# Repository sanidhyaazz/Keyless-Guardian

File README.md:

<h1>Keyless Guardian</h1>

<p>The project aims at implementing a system to mark attendance and grant access to the A.T.O.M. Robotics Laboratory to its members using rfid mechanism that checks the database managed at mongoDB for validating rfid card provided to the members.
It uses hardware technologies like esp32, rfid sensors and pcb designed and managed by the members of the club.
</p>

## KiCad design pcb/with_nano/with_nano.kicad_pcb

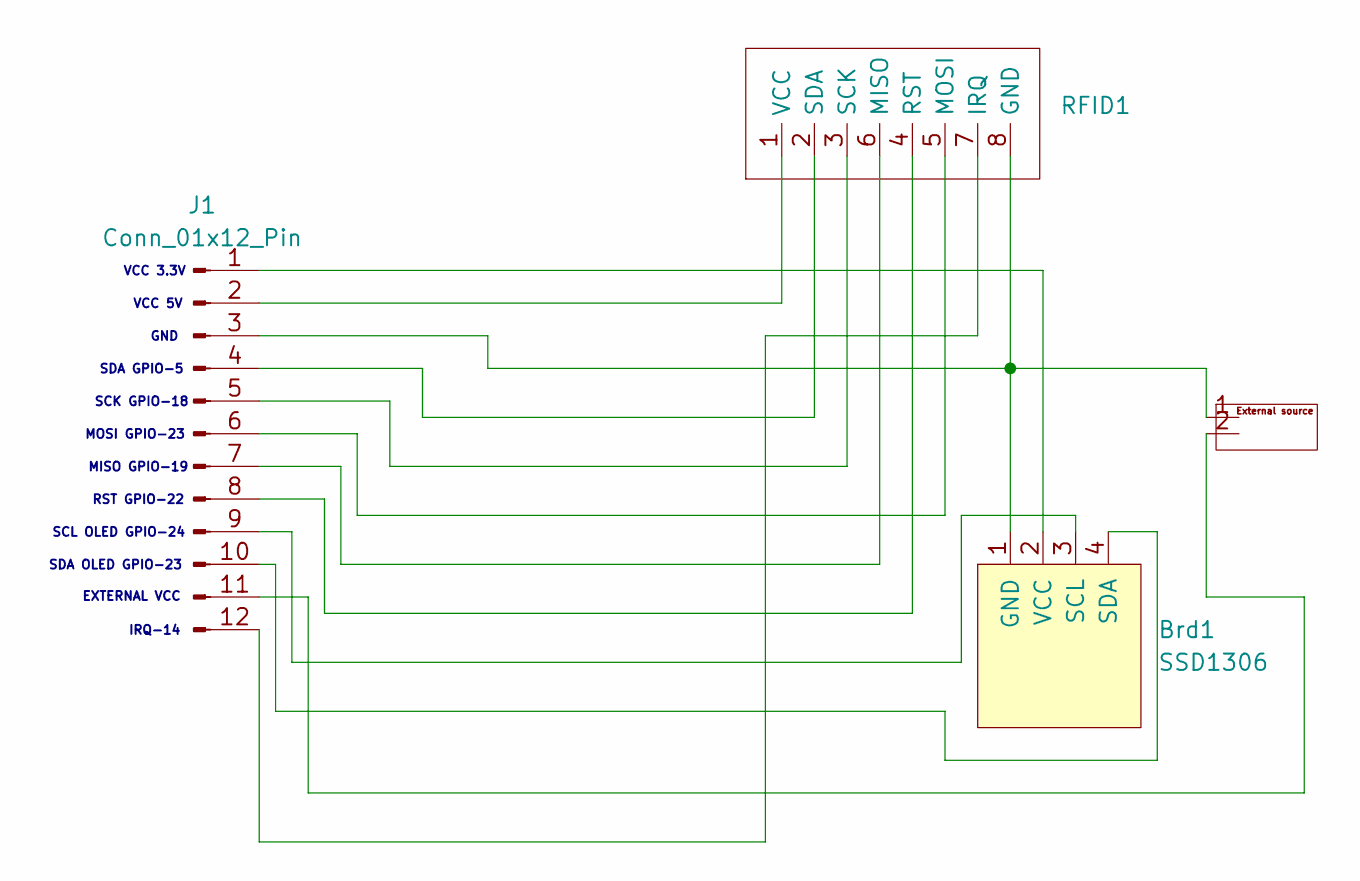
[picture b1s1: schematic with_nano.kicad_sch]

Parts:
Brd1: SSD1306; Adafruit_SSD1306
J1: Conn_01x12_Pin; PinHeader_1x12_P1.00mm_Vertical
RFID1: RFID-RC522
U1: PinSocket_1x02_P1.00mm_Vertical

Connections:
unnamed: Brd1.1 (GND), J1.3, RFID1.8 (GND), U1.1
unnamed: Brd1.3 (SCL), J1.9
unnamed: Brd1.4 (SDA), J1.10
unnamed: Brd1.2 (VCC), J1.1
unnamed: J1.2, RFID1.1 (VCC)
unnamed: J1.4, RFID1.2 (SDA)
unnamed: J1.5, RFID1.3 (SCK)
unnamed: J1.6, RFID1.5 (MOSI)
unnamed: J1.7, RFID1.6 (MISO)
unnamed: J1.8, RFID1.4 (RST)
unnamed: J1.11, U1.2
unnamed: J1.12, RFID1.7 (IRQ)

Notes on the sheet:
MISO GPIO-19
IRQ-14
RST GPIO-22
SDA GPIO-5
SCK GPIO-18
EXTERNAL VCC
GND
SDA OLED GPIO-23
VCC 5V
MOSI GPIO-23
SCL OLED GPIO-24
VCC 3.3V

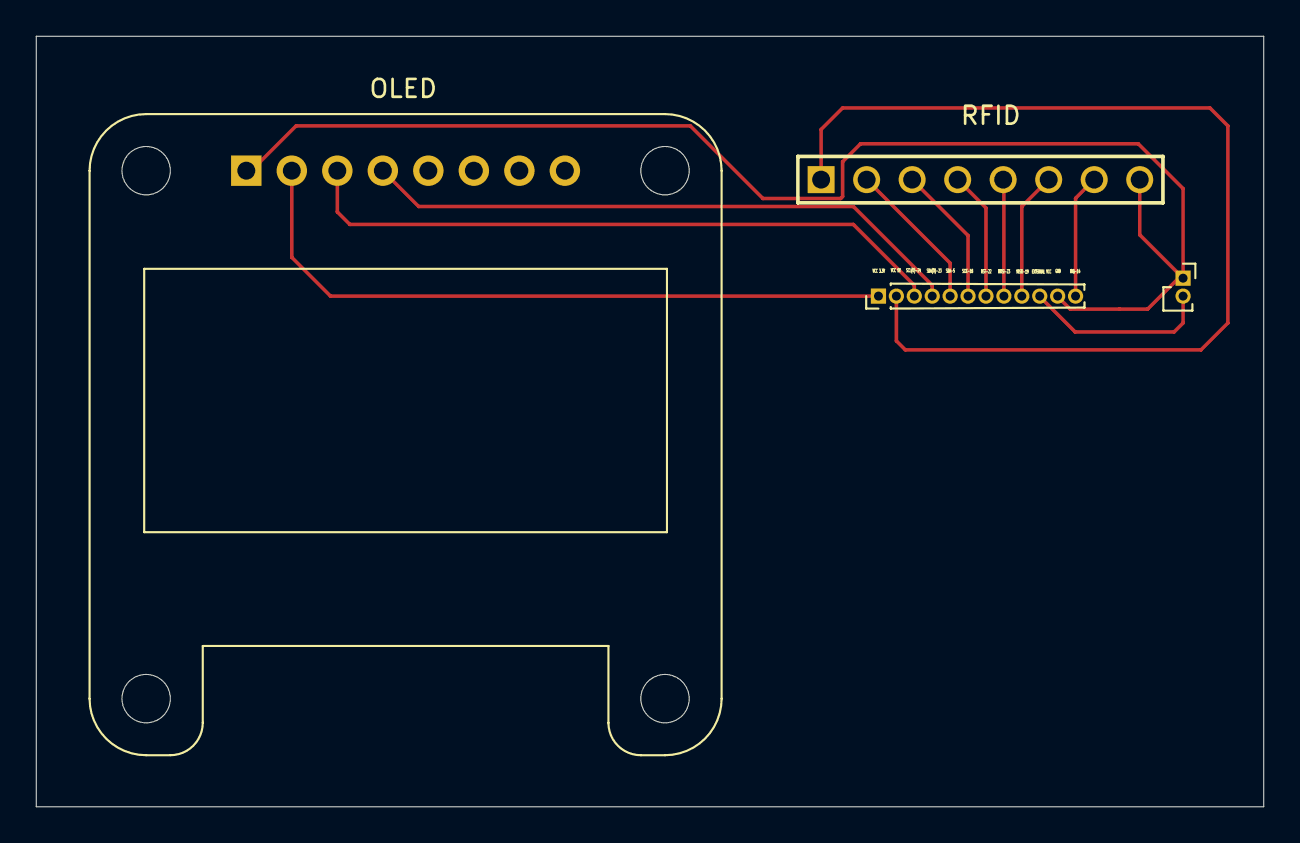
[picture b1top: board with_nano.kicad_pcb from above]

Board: 2 copper layers, 68.5 x 43.0 mm, 4 parts (0 on the bottom side), 12 nets.

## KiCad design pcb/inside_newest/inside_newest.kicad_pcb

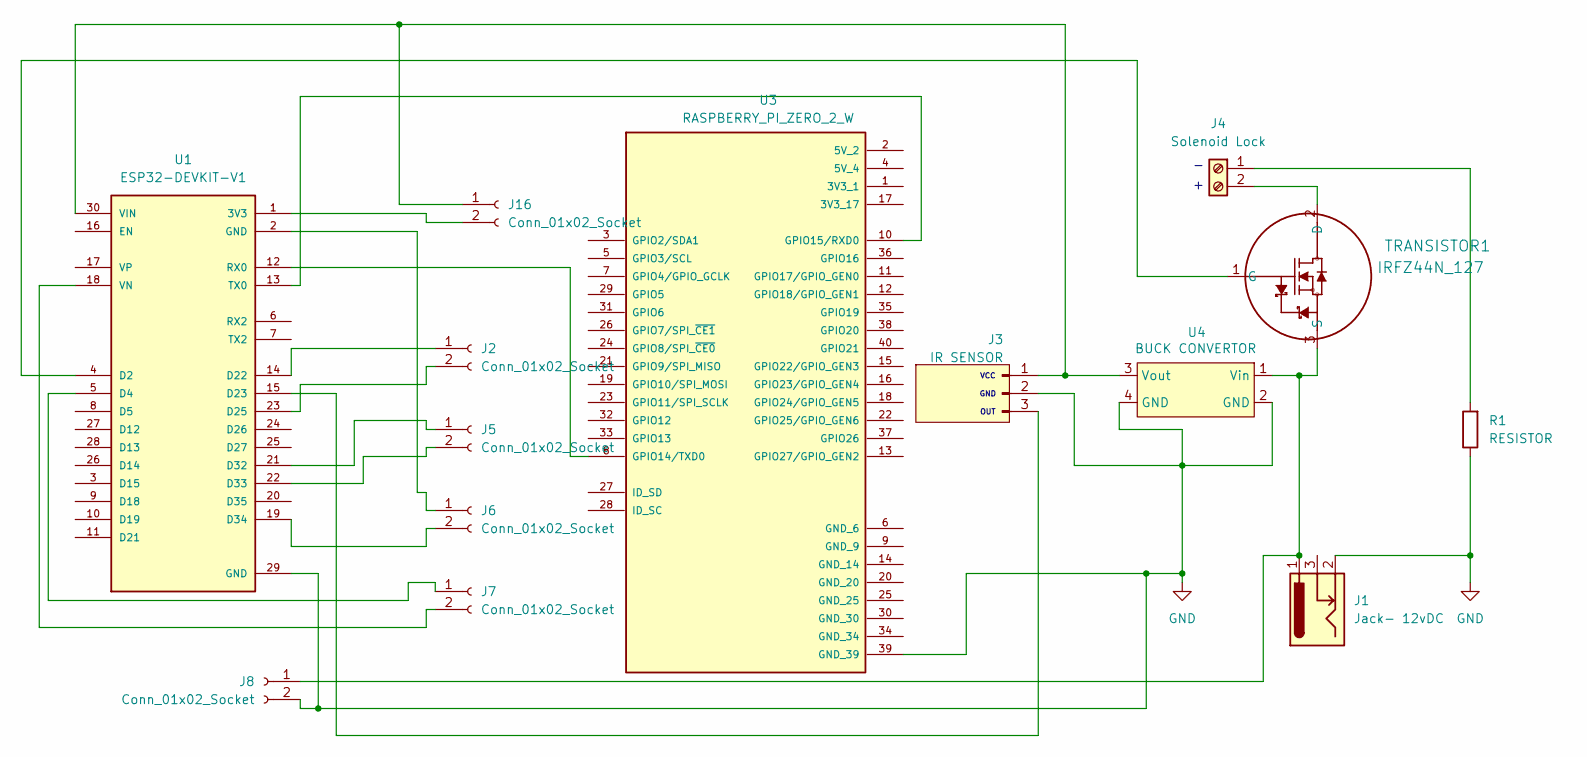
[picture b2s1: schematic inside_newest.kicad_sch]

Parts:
J1: Jack- 12vDC; NINIGI_DC-005
J2, J5, J6, J7, J8, J16: Conn_01x02_Socket; PinSocket_1x02_P1.00mm_Vertical
J3: IR SENSOR; PinSocket_1x03_P1.00mm_Vertical
J4: Solenoid Lock; TerminalBlock_bornier-2_P5.08mm
R1: RESISTOR; PinSocket_1x02_P1.00mm_Vertical
TRANSISTOR1: IRFZ44N_127; SOT78_TO220_NXP
U1: ESP32-DEVKIT-V1; MODULE_ESP32_DEVKIT_V1; PARTREV N/A
U3: RASPBERRY_PI_ZERO_2_W; MODULE_RASPBERRY_PI_ZERO_2_W; PARTREV April 2024
U4: BUCK CONVERTOR; LM2596 DC TO DC BUCK CONVERTER FOOTPRINT

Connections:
GND: J1.2, J3.2, J8.2, R1.1, U1.29 (GND), U3.39 (GND_39), U4.2 (GND), U4.4 (GND)
unnamed: J2.1, U1.14 (D22)
unnamed: J2.2, U1.23 (D25)
unnamed: J3.3, U1.15 (D23)
unnamed: J4.1, R1.2
unnamed: J4.2, TRANSISTOR1.2 (D)
unnamed: J5.1, U1.21 (D32)
unnamed: J5.2, U1.22 (D33)
unnamed: J6.1, U1.2 (GND)
unnamed: J6.2, U1.19 (D34)
unnamed: J7.1, U1.5 (D4)
unnamed: J7.2, U1.18 (VN)
unnamed: J1.1, J8.1, TRANSISTOR1.3 (S), U4.1 (Vin)
unnamed: J3.1, J16.1, U1.30 (VIN), U4.3 (Vout)
unnamed: J16.2, U1.1 (3V3)
unnamed: TRANSISTOR1.1 (G), U1.4 (D2)
unnamed: U1.12 (RX0), U3.8 (GPIO14/TXD0)
unnamed: U1.13 (TX0), U3.10 (GPIO15/RXD0)

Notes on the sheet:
GND
OUT
VCC

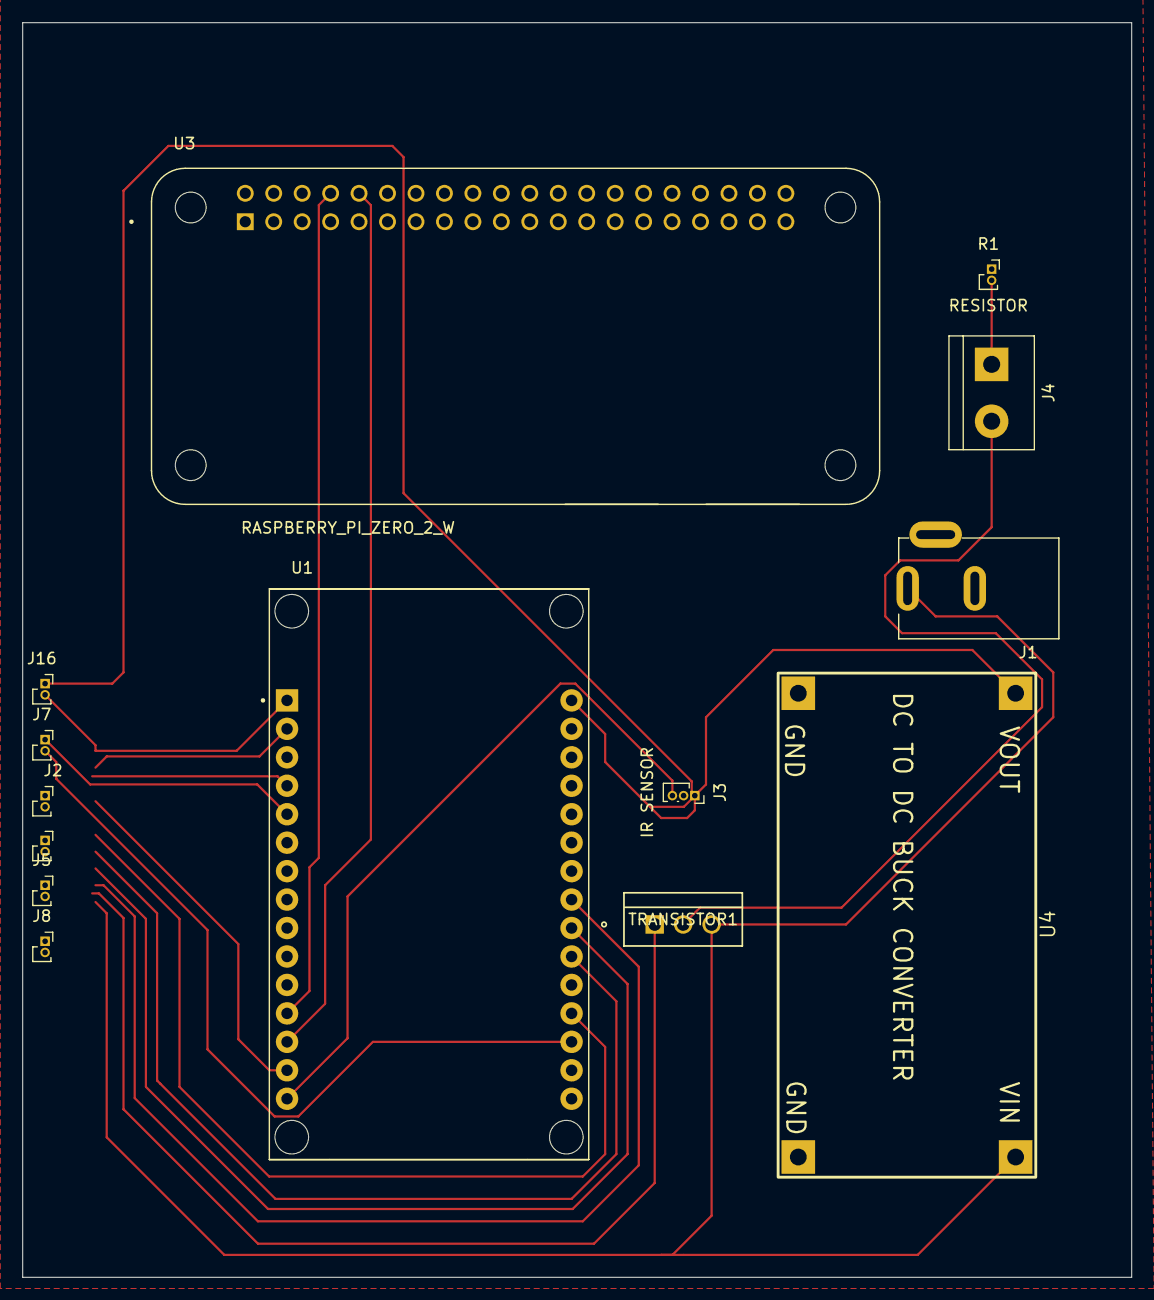
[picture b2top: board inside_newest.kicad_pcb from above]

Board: 2 copper layers, 99.0 x 112.0 mm, 14 parts (0 on the bottom side), 18 nets.

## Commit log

2025-03-18 files added
2026-04-14 readme file
